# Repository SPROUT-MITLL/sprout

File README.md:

# SPROUT

Main repository for SPROUT: an open-source, open-hardware soft robot for search and rescue.

<!-- 📖 **Full documentation, CAD, electronics, and software guides: [sprout-mitll.github.io/sprout](https://sprout-mitll.github.io/sprout/)** -->
📖 **Full documentation, CAD, electronics, and software guides are available in the `docs/` folder of this repository.**

## Repository layout

- [`SPROUT_Design/CAD`](SPROUT_Design/CAD) — SolidWorks/STEP mechanical design files
- [`SPROUT_Design/Code`](SPROUT_Design/Code) — Jetson bootstrap guide and the `sprout_ros` ROS 2 stack
- [`SPROUT_Design/Documentation`](SPROUT_Design/Documentation) — supporting photos and the raw BOM spreadsheet for the Documentation section of the site
- [`SPROUT_Design/Electronics`](SPROUT_Design/Electronics) — custom Arduino shield KiCad project
- [`docs/`](docs) — source for the GitHub Pages documentation site above

## License

Released under the [MIT License](LICENSE).

## Distribution Statement

DISTRIBUTION STATEMENT A. Approved for public release. Distribution is unlimited.
This material is based upon work supported by the Department of the Air Force under Air Force Contract No. FA8702-15-D-0001 or FA8702-25-D-B002. Any opinions, findings, conclusions or recommendations expressed in this material are those of the author(s) and do not necessarily reflect the views of the Department of the Air Force.
<!-- © 2026 Massachusetts Institute of Technology. -->
© 2026 [Institution redacted for double-blind review].

Subject to FAR52.227-11 Patent Rights - Ownership by the contractor (May 2014)
Delivered to the U.S. Government with Unlimited Rights, as defined in DFARS Part 252.227-7013 or 7014 (Feb 2014). Notwithstanding any copyright notice, U.S. Government rights in this work are defined by DFARS 252.227-7013 or DFARS 252.227-7014 as detailed above. Use of this work other than as specifically authorized by the U.S. Government may violate any copyrights that exist in this work.

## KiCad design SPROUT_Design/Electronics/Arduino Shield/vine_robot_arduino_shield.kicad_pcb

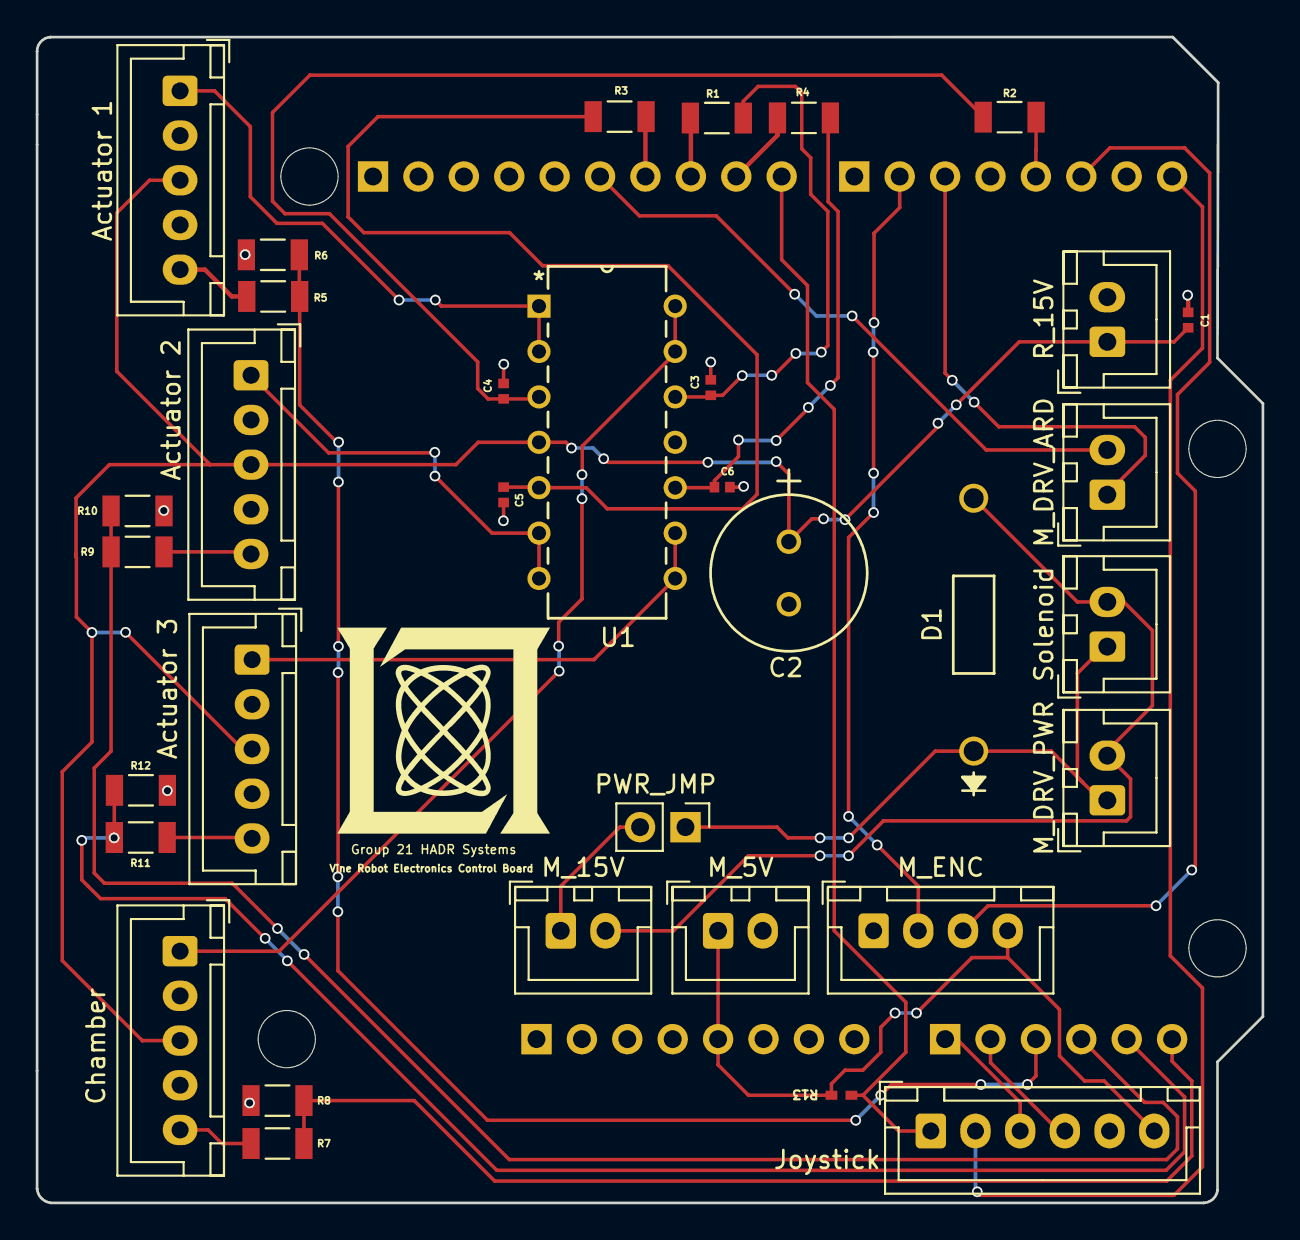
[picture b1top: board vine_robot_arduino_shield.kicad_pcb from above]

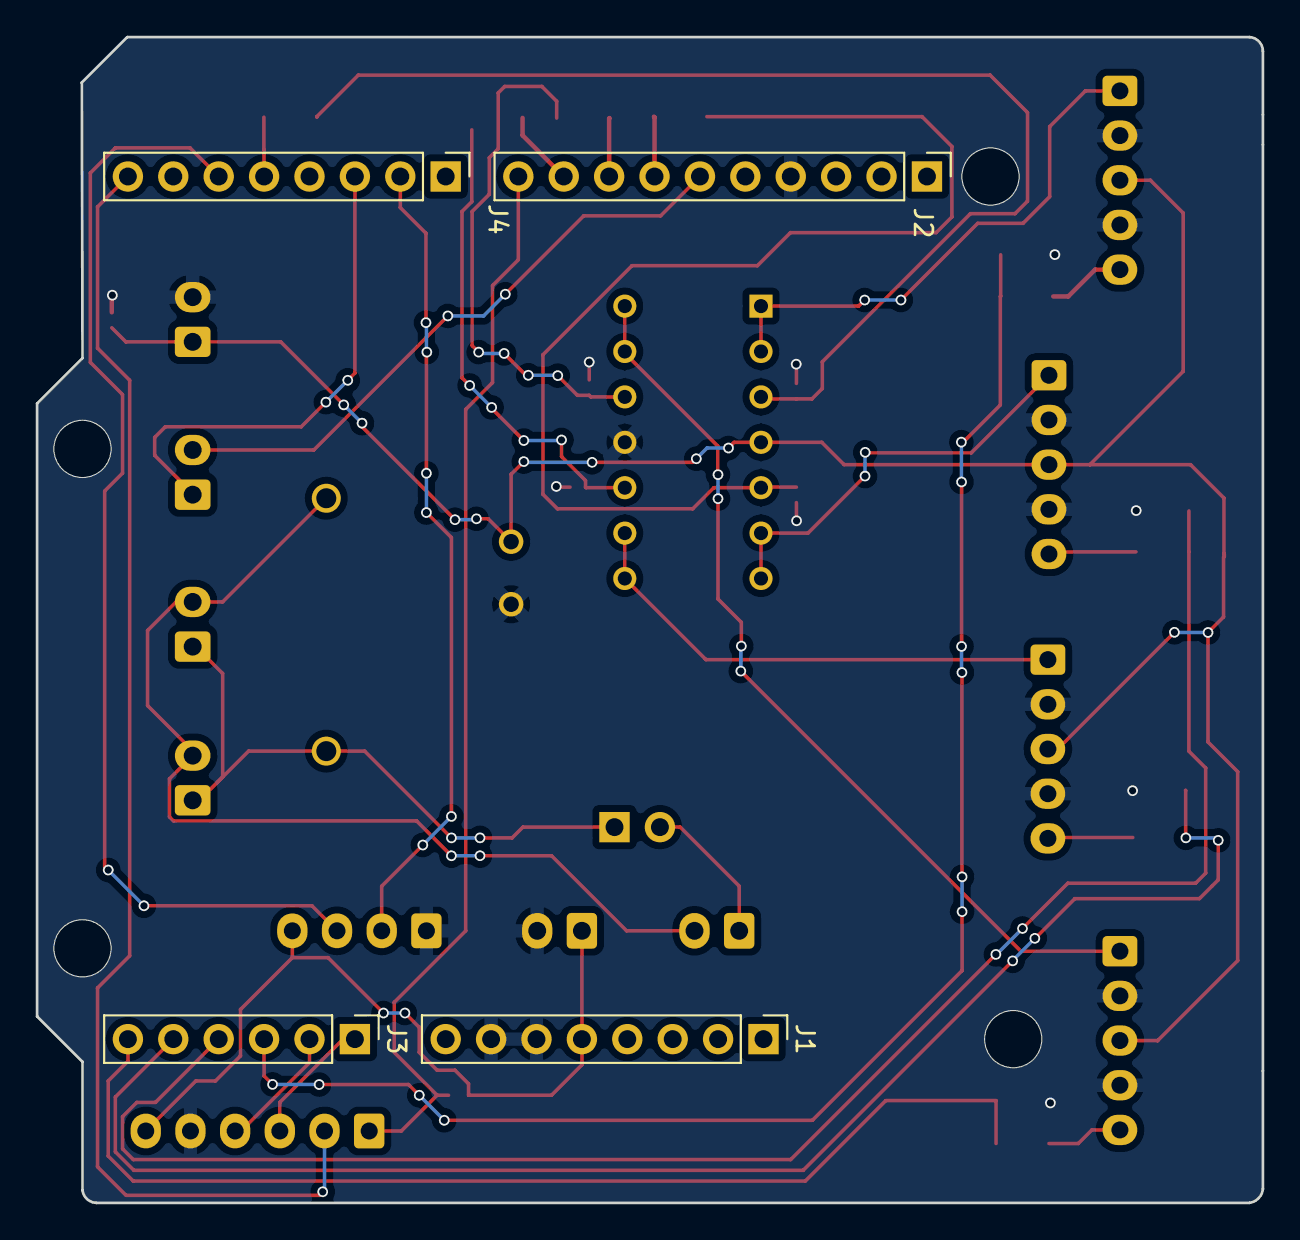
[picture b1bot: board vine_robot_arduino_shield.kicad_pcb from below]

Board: 2 copper layers, 68.6 x 65.2 mm, 42 parts (4 on the bottom side), 34 nets.

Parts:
Actuator 1: Reg1OutConn; JST_XH_B5B-XH-A_1x05_P2.50mm_Vertical
Actuator 2: Reg2OutConn; JST_XH_B5B-XH-A_1x05_P2.50mm_Vertical
Actuator 3: Reg3OutConn; JST_XH_B5B-XH-A_1x05_P2.50mm_Vertical
C1, C3, C4, C5, C6: 0.1µF; CAPC1005X55N
C2: 470µF; CAP_PK&slash_PZ_8X11P5_LOW_RUB
Chamber: RegChambOutConn; JST_XH_B5B-XH-A_1x05_P2.50mm_Vertical
D1: 1N4007; DIO_N4007-T_DIO
J1: Power; PinHeader_1x08_P2.54mm_Vertical
J2: Digital/PWM; PinHeader_1x10_P2.54mm_Vertical
J3: Analog; PinHeader_1x06_P2.54mm_Vertical
J4: Digital/PWM; PinHeader_1x08_P2.54mm_Vertical
Joystick: JoystickConn; JST_XH_B6B-XH-A_1x06_P2.50mm_Vertical
MH1, MH2, MH3, MH4: MountingHole_3.2mm
M_5V: MotorM5V; JST_XH_B2B-XH-A_1x02_P2.50mm_Vertical
M_15V: M15Vin; JST_XH_B2B-XH-A_1x02_P2.50mm_Vertical
M_DRV_ARD: MotorDrvConn; JST_XH_B2B-XH-A_1x02_P2.50mm_Vertical
M_DRV_PWR: MotorDrvPWR; JST_XH_B2B-XH-A_1x02_P2.50mm_Vertical
M_ENC: MotorEncConn; JST_XH_B4B-XH-A_1x04_P2.50mm_Vertical
PWR_JMP: PwrJmpr; PinHeader_1x02_P2.54mm_Vertical
R1, R2, R3, R4: 220kΩ; RESC3116X65N
R5, R6, R7, R8, R9, R10, R11, R12: 10kΩ; RESC3116X65N
R13: 1kΩ; RC0402N_YAG
R_15V: R15Vin; JST_XH_B2B-XH-A_1x02_P2.50mm_Vertical
Solenoid: SolenoidConn; JST_XH_B2B-XH-A_1x02_P2.50mm_Vertical
U1: LM324N; N14

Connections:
+5V: J1.5, Joystick.6, M_5V.1, M_ENC.4, R13.2
+15V: Actuator 1.3, Actuator 2.3, Actuator 3.3, C1.1, C2.1, Chamber.3, R_15V.1, U1.4 (VCC)
/2: J4.6, M_ENC.3
/8: J2.10, Joystick.1, R13.1
/12: J2.6, M_DRV_ARD.2
/*3: J4.5, R2.1
/*5: J4.3, M_DRV_ARD.1
/*6: J4.2, M_ENC.2
/*9: J2.9, R4.1
/*10: J2.8, R1.1
/*11: J2.7, R3.1
/ChambSigIn: C3.1, R1.2, U1.12 (4IN+)
/JoyAnalog1: J3.1, Joystick.3
/JoyAnalog2: J3.2, Joystick.4
/JoyDigi2: J4.8, Joystick.2
/Reg1MonIn: Actuator 1.5, R5.1
/Reg1MonOut: J3.3, R5.2, R6.1
/Reg1Out: Actuator 1.1, U1.1 (1OUT), U1.2 (1IN-)
/Reg1SigIn: C4.1, R2.2, U1.3 (1IN+)
/Reg2MonIn: Actuator 2.5, R9.1
/Reg2MonOut: J3.4, R9.2, R10.1
/Reg2Out: Actuator 2.1, U1.6 (2IN-), U1.7 (2OUT)
/Reg2SigIn: C5.1, R3.2, U1.5 (2IN+)
/Reg3MonIn: Actuator 3.5, R11.1
/Reg3MonOut: J3.5, R11.2, R12.1
/Reg3Out: Actuator 3.1, U1.8 (3OUT), U1.9 (3IN-)
/Reg3SigIn: C6.1, R4.2, U1.10 (3IN+)
/RegChambMonIn: Chamber.5, R7.1
/RegChambMonOut: J3.6, R7.2, R8.1
/RegChambOut: Chamber.1, U1.13 (4IN-), U1.14 (4OUT)
GND: Actuator 1.2, Actuator 1.4, Actuator 2.2, Actuator 2.4, Actuator 3.2, Actuator 3.4, C1.2, C2.2, C3.2, C4.2, C5.2, C6.2, Chamber.2, Chamber.4, J1.6, J1.7, J2.4, Joystick.5, M_5V.2, M_ENC.1, R6.2, R8.2, R10.2, R12.2, R_15V.2, U1.11 (GND)
unnamed: D1.1, M_DRV_PWR.1, PWR_JMP.1, Solenoid.1
unnamed: M_15V.1, PWR_JMP.2
unnamed: D1.2, M_15V.2, M_DRV_PWR.2, Solenoid.2
